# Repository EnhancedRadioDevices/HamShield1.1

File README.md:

HamShield1.1 Hardware

You can purchase HamShield (as well as smaller variants or LoRa version) at http://www.enhancedradio.com/

These are the hardware design files for the HamShield1.1 electronics.

Primary changes from the HamShield1.0b hardware are the RF switches that control what band is active. The entire shield is still compatible with the Arduino library.

These hardware files were created with KiCAD.

You may need the KiCAD libraries available here: https://github.com/mogar/KiCAD_libs
When opening these projects in KiCAD, you may need to change the path to the libraries from the above link.
This can be done in preferences->libraries in both the schematic editor and the layout editor.
Make sure the libraries noted there point to wherever you put the above KiCAD_libs repo.

The Arduino Library for this project is available here: https://github.com/EnhancedRadioDevices/HamShield

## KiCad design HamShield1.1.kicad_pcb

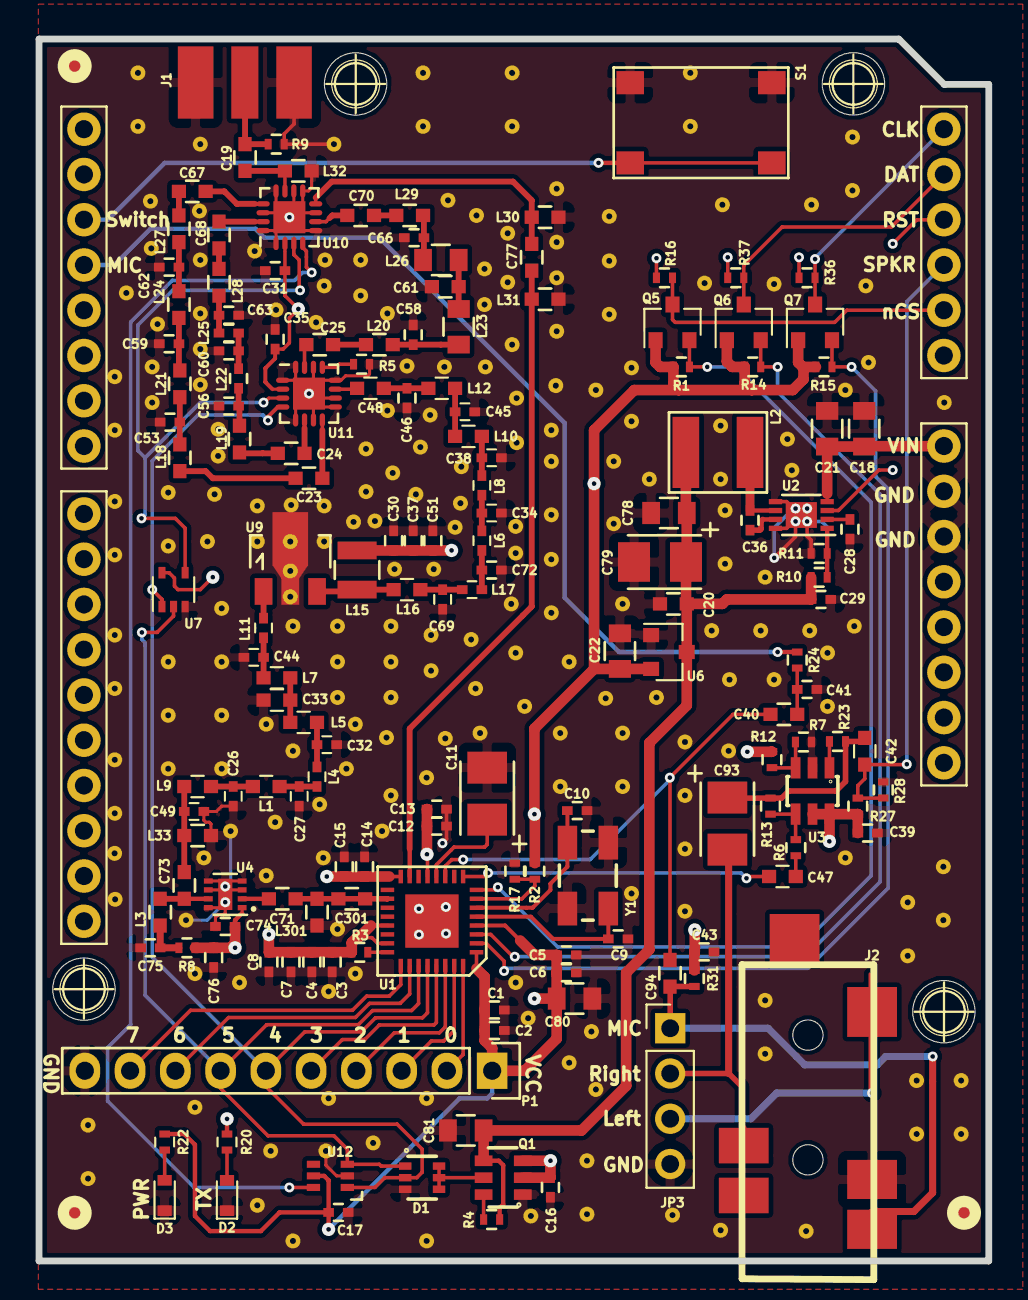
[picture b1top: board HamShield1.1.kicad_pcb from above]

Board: 4 copper layers, 53.3 x 68.6 mm, 162 parts (0 on the bottom side), 95 nets.

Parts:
C1, C3, C5, C7, C12, C14, C30: 1n; C_0402
C2, C4, C6, C8, C16, C17, C31, C35, C36, C37, C39, C43, C74, C75, C76: 0u1; C_0402
C9, C10, C15: 10p; C_0402
C11, C79, C93: 47u; C1210P
C13, C28, C29, C51: 1u; C_0402
C18, C21, C22, C78, C80: 10u; C_0805
C19, C23, C24, C25, C48, C67, C68, C70, C71, C73, C77: 100p; C_0603
C20: 4.7u; C_0603
C26, C38, C53, C62: 7p; C_0402
C27: 8p; C_0402
C32, C56, C63, C72: 14p; C_0402
C33, C61: 24p; C_0603
C34: 11p; C_0402
C40, C42, C47, C94: 2u2; C_0603
C41: 15n; C_0402
C44: 47p; C_0402
C45: 5.1p; C_0402
C46, C49: 2.2p; C_0402
C58, C66: 20p; C_0402
C59: 8.2p; C_0402
C60, C69: 15p; C_0402
C81: 22u; C_0805
C301: DNP; C_0603
D1: BAS40TW; SOT-363
D2, D3: LED; D_0603
FD1, FD2, FD3: FIDUCIAL1X2.5; SparkFun-FIDUCIAL-1X2.5
J1: SMA_EDGE; SMA-EDGE-HandSolder
J2: SJ-43514-SMT-TR
JP3: M04PTH; Pin_Header_Straight_1x04_Pitch2.54mm
L1, L10: 5.6n; C_0603
L2: NR5040T220M; NR5040
L3: 220n; C_0603
L4, L8: 3.9n; C_0402
L5: 3n; C_0603
L6: 3.6n; C_0402
L7, L16: 2n; C_0603
L9, L12: 6.2n; C_0603
L11: 0ohm; C_0402
L15: 100n; L_1008
L17: 3.3n; C_0402
L18, L27: 24n; C_0603
L19, L28: 47n; C_0603
L20, L29: 82n; C_0603
L21, L24: 33n; C_0603
L22, L25: 75n; C_0402
L23, L26: 120n; C_0805
L30, L31, L32, L33, L301: DNP; C_0603
P1: Conn_01x10_Male; Pin_Header_Straight_1x10
Q1: NTGD1100L; SC-74
Q5, Q6, Q7: BSS138; SOT-23
R1, R4, R6, R7, R9, R11, R12, R13, R14, R15, R16, R36, R37: 10k; R_0402
R2, R3: 0; R_0402
R5: 49.9; R_0402
R8: 1.8; R_0402
R10: 52.3k; R_0402
R17: DNP; R_0402
R20, R22: 330; R_0402
R23: 13.3; R_0402
R24: 1.47k; R_0402
R27, R28: 100k; R_0402
R31: 2k; R_0402
S1: TAC_SWITCHSMD; SWITCH_TACTILE_SMD_8mmX5mm
U1: AU1846; QFN32-5x5
U2: MCP16311; DFN-8-1EP_3x2mm_Pitch0.5mm
U3: AD8591; SOT23-6
U4: TRF37A75; DFN-8-1EP_2x2mm_Pitch0.5mm
U5: ARDUINO_SHIELD; ARDUINO_UNO_SHIELD
U6: AP2125N-3.3TRG1; SOT-23
U7: NC7SZ86; SOT-353_SC-70-5
U9: TQP7M9105; SOT89-3_Housing
U10, U11: PE42440; QFN-16-1EP_3x3mm_Pitch0.5mm
U12: NC7WZ14; SC-70-6
Y1: 12.8MHz; CRYSTAL-SMD-5X3

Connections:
+5V: C20.1, C29.2, C78.2, C79.1, C81.2, L2.2, Q1.4, R4.1, R10.1, U6.3
+5VL: R16.2, R36.2, R37.2, U5.5V
/AFOUT: C47.1, U1.9
/CLK: Q7.2, R15.1, U1.2
/DAT: Q6.2, R14.1, U1.3
/GPIO0: P1.2, U1.32
/GPIO1: P1.3, U1.31
/GPIO2: P1.4, U1.30
/GPIO3: P1.5, U1.29
/GPIO4: D1.2, P1.6, U1.28, U7.1, U11.4, U12.1
/GPIO5: D1.1, P1.7, U1.27, U7.2, U12.3
/GPIO6: P1.8, U1.26
/GPIO7: P1.9, U1.25
/MIC_IN: C40.1, C94.1, U1.11
/MODE: R2.1, R17.1, U1.7
/PDN: R3.1, U1.24
/RF Front End/1.2m_IN: C24.1, U11.6
/RF Front End/1.2m_OUT: C68.1, U10.15
/RF Front End/2m_IN: C25.1, U11.15
/RF Front End/2m_OUT: C70.1, U10.6
/RF Front End/70cm_IN: C23.1, U11.8
/RF Front End/70cm_OUT: C67.1, U10.13
/RF Front End/ANT: C19.1, L32.2, U10.11
/RF Front End/RF_OUT: C71.2, C301.1, C301.2, L301.2, U1.18
/RF Front End/S2_IN: L11.2, U9.1
/RF Front End/STAGE1_OUT: C49.1, C73.1, L9.1, L33.2
/RF Front End/STAGE2_OUT: C48.2, U11.11
/RF Front End/V1xorV2: U7.4, U10.3, U11.3
/RFin: C77.1, L31.1, U1.15
/User Interface/ARD_AUDIO_OUT: C42.2, R27.1, R28.1, U5.A2
/User Interface/PWM_AUDIO_IN: R24.2, U5.D3
/Y1: U10.4, U12.6
/nCS: Q5.2, R1.1, U1.8
/nRST: U2.3, U5.A3
GND: C1.2, C2.2, C3.2, C4.2, C5.2, C6.2, C7.2, C8.2, C9.2, C10.2, C11.2, C12.2, C13.2, C14.2, C15.2, C16.2, C17.1, C18.2, C20.2, C21.2, C22.1, C26.2, C27.2, C28.2, C29.1, C30.2, C31.2, C32.2, C33.2, C34.2, C35.2, C37.2, C38.2, C39.1, C41.1, C43.1, C44.2, C45.2, C46.2, C49.2, C51.2, C53.2, C56.2, C58.2, C59.2, C60.2, C61.2, C62.2, C63.2, C66.2, C69.2, C72.2, C74.2, C75.2, C76.2, C78.1, C79.2, C80.1, C81.1, D1.3, D2.1, D3.1, J1.GND, J2.4, JP3.4, L30.2, L31.2, L32.1, L33.1, L301.1, P1.10, Q1.1, R5.1, R7.2, R9.2, R11.2, R17.2, R28.2, S1.3, S1.4, U1.33, U2.5, U2.8, U2.9, U3.2, U4.3, U4.4, U4.5, U4.6, U4.8, U4.9, U5.GP1, U5.GP2, U6.1, U7.3, U9.2, U10.1, U10.5, U10.7, U10.9, U10.10, U10.12, U10.14, U10.16, U10.17, U11.1, U11.5, U11.7, U11.9, U11.10, U11.12, U11.14, U11.16, U11.17, U12.2, Y1.2, Y1.4
unnamed: C9.1, U1.5, Y1.1
unnamed: C10.1, U1.6, Y1.3
unnamed: C11.1, U1.12
unnamed: C19.2, J1.SIG, R9.1
unnamed: C23.2, L18.2
unnamed: C24.2, L19.2
unnamed: C25.2, L20.2
unnamed: C26.1, L1.1, L9.2
unnamed: C27.1, L1.2, L4.1
unnamed: C28.1, U2.2
unnamed: C32.1, L4.2, L5.1
unnamed: C33.1, L5.2, L7.1
unnamed: C34.1, L6.1, L8.2
unnamed: C36.1, U2.7
unnamed: C36.2, L2.1, U2.6
unnamed: C38.1, L8.1, L10.2
unnamed: C40.2, C41.2, R24.1
unnamed: C42.1, C93.1, R13.2, R23.2
unnamed: C44.1, L7.2, L11.1
unnamed: C45.1, L10.1, L12.2
unnamed: C46.1, C48.1, L12.1
unnamed: C47.2, R6.1
unnamed: C53.1, L18.1, L21.2
unnamed: C56.1, L19.1, L22.2
unnamed: C58.1, L20.1, L23.2
unnamed: C59.1, L21.1, L24.2
unnamed: C60.1, L22.1, L25.2
unnamed: C61.1, L23.1, L26.2
unnamed: C62.1, L24.1, L27.2
unnamed: C63.1, L25.1, L28.2
unnamed: C66.1, L26.1, L29.2
unnamed: C67.2, L27.1
unnamed: C68.2, L28.1
unnamed: C69.1, L16.1, L17.2
unnamed: C70.2, L29.1
unnamed: C71.1, U4.2
unnamed: C72.1, L6.2, L17.1
unnamed: C73.2, L3.1, U4.7
unnamed: C75.1, L3.2, R8.1
unnamed: C77.2, L30.1, U10.8
unnamed: C93.2, J2.3, JP3.2
unnamed: C94.2, J2.1, JP3.1, R31.2
unnamed: D1.4, D1.5, D1.6, Q1.5
unnamed: D2.2, R20.2
unnamed: D3.2, R22.2
unnamed: J2.2, JP3.3
unnamed: L15.1, L16.2, U9.3
unnamed: Q1.6, R4.2
unnamed: Q5.3, R16.1, U5.A1
unnamed: Q6.3, R37.1, U5.A4
unnamed: Q7.3, R36.1, U5.A5
unnamed: R5.2, U11.13
unnamed: R10.2, R11.1, U2.1
unnamed: R7.1, R12.2, U3.3
unnamed: R6.2, R13.1, U3.4
unnamed: R23.1, U3.1
unnamed: S1.1, S1.2, U5.D2
VCC: C1.1, C2.1, C3.1, C4.1, C5.1, C6.1, C7.1, C8.1, C12.1, C13.1, C14.1, C15.1, C17.2, C22.2, C31.1, C35.1, C39.2, C80.2, P1.1, Q5.1, Q6.1, Q7.1, R1.2, R2.2, R3.2, R12.1, R14.2, R15.2, R22.1, R27.2, U1.1, U1.4, U1.13, U1.16, U1.21, U1.23, U3.5, U3.6, U6.2, U7.5, U10.2, U11.2, U12.5
VIN: C18.1, C21.1, U2.4, U5.VIN
VTX: C16.1, C30.1, C37.1, C43.2, C51.1, C74.1, C76.1, L15.2, Q1.2, Q1.3, R8.2, R20.1, R31.1, U4.1

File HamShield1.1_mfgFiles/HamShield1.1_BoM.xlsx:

Id | Designator | Package | Quantity | Designation | Mfg | Mfg PN | Distributor | Dist PN
1 | U11,U10 | QFN-16-1EP_3x3mm_Pitch0.5mm | 2 | PE42440 | pSemi | PE42440MLBB-Z | DigiKey | 1046-1038-1-ND
2 | J2 | SJ-43514-SMT-TR | 1 | SJ-43514-SMT-TR | CUI | SJ-43514-SMT-TR | DigiKey | CP-43514SJDKR-ND
3 | U1 | QFN32-5x5 | 1 | AU1846 | Auctus | AU1846 | Auctus | AU1846
4 | U3 | SOT23-6 | 1 | AD8591 | Analog Devices | AD8591ARTZ-REEL7 | DigiKey | AD8591ARTZ-REEL7DKR-ND
5 | S1 | SWITCH_TACTILE_SMD_8mmX5mm | 1 | TAC_SWITCHSMD | C&K | PTS645SM43SMTR92 LFS | DigiKey | CKN9112DKR-ND
6 | C44 | C_0402 | 1 | 47p | Murata | GJM1555C1H470JB01D | DigiKey | 490-14446-2-ND
7 | C46,C49 | C_0402 | 2 | 2.2p | Murata | GJM1555C1H2R2CB01D | DigiKey | 490-3091-2-ND
8 | L15 | C_1008 | 1 | 100n | Abracon | AISC-1008HQ-R10J-T | DigiKey | 535-12247-2-ND
9 | P1 | Pin_Header_Straight_1x10 | 1 | CONN_01X10 | DNP | DNP | DNP | DNP
10 | C20 | C_0603 | 1 | 4.7u | Yageo | CC0603KRX5R6BB475 | DigiKey | 311-1455-2-ND
11 | U9 | SOT89-3_Housing | 1 | TQP7M9105 | Qorvo | TQP7M9105 | Mouser | 772-TQP7M9105
12 | C1,C3,C5,C7,C12,C14,C30 | C_0402 | 7 | 1n | Yageo | CC0402KRX7R9BB102 | DigiKey | 311-1036-6-ND
13 | C2,C4,C6,C8,C16,C17,C31,C35,C36,C37,C39,C43,C75,C76,C74 | C_0402 | 15 | 0u1 | Taiyo-Yuden | LMK105BJ104KV-F | DigiKey | 587-1227-1-ND
14 | C9,C10,C15 | C_0402 | 3 | 10p | Murata | GJM1555C1H100JB01D | DigiKey | 490-3113-2-ND
15 | C13,C51,C28,C29 | C_0402 | 4 | 1u | Murata | GRM155R61A105KE15J | DigiKey | 490-6298-2-ND
16 | C19,C23,C24,C25,C48,C67,C73,C68,C70,C71,C77 | C_0603 | 11 | 100p | Johanson | 251R14S101JV4T | DigiKey | 712-1310-2-ND
17 | C40,C42,C47,C94 | C_0603 | 4 | 2u2 | Taiyo-Yuden | JMK107BJ225KAHT | DigiKey | 587-3386-6-ND
18 | C41 | C_0402 | 1 | 15n | Samsung | CL05F153ZA5NNNC | DigiKey | 1276-1742-2-ND
20 | C56,C63,C72,C32 | C_0402 | 4 | 14p | AVX | 04025U140GAT2A | Mouser | 581-04025U140GAT2A
21 | C59 | C_0402 | 1 | 8.2p | Murata | GJM1555C1H8R2CB01D | DigiKey | 490-3110-2-ND
22 | C60,C69 | C_0402 | 2 | 15p | Murata | GJM1555C1H150JB01D | DigiKey | 490-3117-2-ND
24 | R3,R2 | R_0402 | 2 | 0 | Vishay Dale | CRCW04020000Z0ED | DigiKey | 541-0.0JDKR-ND
25 | R12,R13,R36,R37,R4,R6,R7,R9,R11,R1,R14,R15,R16 | R_0402 | 13 | 10k | TE Connectivity | 1622826-4 | DigiKey | A106045TR-ND
27 | R23 | R_0402 | 1 | 13.3 | Vishay Dale | CRCW040213R3FKED | DigiKey | 541-13.3LDKR-ND
28 | R24 | R_0402 | 1 | 1.47k | Yageo | RC0402FR-071K47L | DigiKey | YAG3038TR-ND
29 | R27,R28 | R_0402 | 2 | 100k | Vishay Dale | CRCW0402100KJNED | DigiKey | 541-100KJDKR-ND
30 | R31 | R_0402 | 1 | 2k | Vishay Dale | CRCW04022K00JNED | DigiKey | 541-2.0KJDKR-ND
33 | Q1 | SC-74 | 1 | NTGD1100L | ON Semi | NTGD1100L | DigiKey | NTGD1100LT1GOSTR-ND
34 | R5 | R_0402 | 1 | 49.9 | Yageo | RC0402FR-0749R9L | DigiKey | 311-49.9LRTR-ND
35 | D1 | SOT-363 | 1 | BAS40TW | Diodes Inc. | BAS40TW | DigiKey | BAS40TW-FDITR-ND
36 | C58,C66 | C_0402 | 2 | 20p | Murata | GJM1555C1H200JB01D | DigiKey | 490-3120-2-ND
37 | U12 | SC-70-6 | 1 | NC7WZ14 | Fairchild Semi | NC7WZ14 | DigiKey | NC7WZ14P6XTR-ND
38 | C61,C33 | C_0603 | 2 | 24p | Murata | GQM1885C1H240GB01D | DigiKey | 490-8131-2-ND
39 | L18,L27 | C_0603 | 2 | 24n | Murata | LQW18AN24NJ00D | DigiKey | 490-6878-2-ND
40 | L19,L28 | C_0603 | 2 | 47n | Bourns | CW160808-47NJ | DigiKey | CW160808-47NJTR-ND
41 | L21,L24 | C_0603 | 2 | 33n | Murata | LQW18AN33NJ00D | DigiKey | 490-1175-2-ND
42 | C34 | C_0402 | 1 | 11p | Murata | GJM1555C1H110GB01D | DigiKey | 490-6072-2-ND
44 | C53,C62,C38,C26 | C_0402 | 4 | 7p | Murata | GJM1555C1H7R0CB01D | DigiKey | 490-3107-2-ND
45 | L1,L10 | C_0603 | 2 | 5.6n | Murata | LQW18AN5N6D00D | DigiKey | 490-1164-2-ND
46 | L5 | C_0603 | 1 | 3n | Murata | LQW18AN3N0C80D | DigiKey | 490-11771-2-ND
47 | L9,L12 | C_0603 | 2 | 6.2n | Murata | LQW18AN6N2D00D | DigiKey | 490-1163-2-ND
48 | L16,L7 | C_0603 | 2 | 2n | Johanson | L-14W2N0CV4E | DigiKey | 712-1618-2-ND
49 | L22,L25 | C_0402 | 2 | 75n | Murata | LQW15AN75NJ00D | DigiKey | 490-6843-1-ND
50 | L23,L26 | C_0805 | 2 | 120n | Bourns | PM0805-R12K-RC | DigiKey | M8464TR-ND
51 | R8 | R_0402 | 1 | 1.8 | Vishay Dale | CRCW04021R80JNED | DigiKey | 541-1.8JCT-ND
53 | C11,C79,C93 | C1210P | 3 | 47u | AVX | TAJB476K010RNJ | DigiKey | 478-1693-2-ND
54 | U4 | DFN-8-1EP_2x2mm_Pitch0.5mm | 1 | TRF37A75 | TI | TRF37A75 | DigiKey | 296-37886-1-ND
55 | L30,L31,L32,L33,C301,L301 | C_0603 | 6 | DNP
56 | R10 | R_0402 | 1 | 52.3k | Vishay Dale | CRCW040252K3FKED | DigiKey | 541-52.3KLCT-ND
57 | C18,C21,C78,C22,C80 | C_0805 | 5 | 10u | Murata | GRM21BR61E106KA73L | DigiKey | 490-5523-2-ND
58 | L2 | NR5040 | 1 | NR5040T220M | Taiyo-Yuden | NR5040T220M | DigiKey | 587-2368-2-ND
59 | L3 | C_0603 | 1 | 220n | TE Connectivity | 9-1624112-0 | DigiKey | A103722CT-ND
60 | L17 | C_0402 | 1 | 3.3n | Murata | LQW15AN3N3D10D | DigiKey | 490-6809-2-ND
61 | L20,L29 | C_0603 | 2 | 82n | Bourns | PM0603-82NJ-RC | DigiKey | M8491TR-ND
62 | C81 | C_0805 | 1 | 22u | Samsung | CL21A226MQQNNNE | DigiKey | 1276-1100-2-ND
63 | U2 | DFN-8-1EP_3x2mm_Pitch0.5mm | 1 | MCP16311 | Microchip | MCP16311T-E/MNY | Mouser | 579-MCP16311T-E/MNY
64 | J1 | SMA-EDGE-HandSolder | 1 | DNP | Linx | CONSMA003.062 | DigiKey | CONSMA003.062-ND
65 | R17 | R_0402 | 1 | DNP
66 | D2,D3 | D_0603 | 2 | LED | Lite-On | LTST-C190KGKT | DigiKey | 160-1435-2-ND
68 | R20,R22 | R_0402 | 2 | 330 | Yageo | RC0402JR-07330RL | DigiKey | 311-330JRTR-ND
69 | C27 | C_0402 | 1 | 8p | Murata | GJM1555C1H8R0CB01D | DigiKey | 490-3109-2-ND
70 | C45 | C_0402 | 1 | 5.1p | Murata | GJM1555C1H5R1CB01D | DigiKey | 490-3102-2-ND
71 | L4,L8 | C_0402 | 2 | 3.9n | Murata | LQW15AN3N9C00D | DigiKey | 490-6813-2-ND
72 | L6 | C_0402 | 1 | 3.6n | Abracon | AISC-0402-3N6G-T | DigiKey | AISC-0402-3N6G-TTR-ND
74 | L11 | C_0402 | 1 | 0ohm | Vishay Dale | CRCW04020000Z0ED | DigiKey | 541-0.0JDKR-ND
77 | JP3 | Pin_Header_Straight_1x04_Pitch2.54mm | 1 | DNP
78 | Q5,Q6,Q7 | SOT-23 | 3 | BSS138 | Fairchild Semi | BSS138 | DigiKey | BSS138TR-ND
79 | U6 | SOT-23 | 1 | AP2125N-3.3TRG1 | Diodes Inc. | AP2125N-3.3TRG1 | DigiKey | AP2125N-3.3TRG1DITR-ND
80 | Y1 | CRYSTAL-SMD-5X3 | 1 | 12.8MHz | CTS | 405C11A12M80000 | DigiKey | CTX957DKR-ND
81 | U7 | SOT-353_SC-70-5 | 1 | NC7SZ86 | ON Semi | NC7SZ86P5X | DigiKey | NC7SZ86P5XCT-ND

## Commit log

2019-03-16 update schematic
